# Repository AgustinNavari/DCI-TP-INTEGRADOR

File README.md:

# Shield de motor paso a paso para Arduino Nano ESP32

Trabajo práctico integrador de la asignatura Diseño de Circuitos Impresos del posgrado de FIUBA.

- **Autor:** Agustín Navari
- **Cursada:** octubre–diciembre de 2026
- **Driver:** Toshiba TB67S249FTG
- **Plataforma:** Arduino Nano ESP32
- **Estado:** diseño del PCB y ruteo en desarrollo.

## Descripción y objetivo

El proyecto consiste en el diseño de una placa para controlar un motor paso a paso bipolar mediante un Arduino Nano ESP32, utilizando el driver TB67S249FTG.

El diseño toma como referencia el módulo Pololu 2973 y adapta sus interfaces al formato de una placa portadora para el Nano ESP32. Incluye dos conectores hembra de 15 posiciones para alojar el módulo y un conector adicional de 2 × 15 posiciones que permite acceder a sus pines.

El objetivo es desarrollar el esquemático, seleccionar los componentes y diseñar el PCB, contemplando los requisitos eléctricos, térmicos, mecánicos y de fabricación.

## Características del diseño

- Alimentación del motor de 24 V nominales.
- Alimentación del Nano mediante USB o una entrada externa independiente.
- Protección contra inversión de polaridad en la alimentación del motor mediante un MOSFET.
- Control de movimiento mediante las señales STEP, DIR y ENABLE.
- Configuración de funciones del driver mediante jumpers.
- Conexión opcional de señales de configuración al Nano.
- Ajuste del límite de corriente mediante potenciómetro.
- Conector independiente para las salidas de diagnóstico.
- PCB de dos capas, previsto para cobre de 1 oz y espesor de placa de 1,6 mm.

## Interfaz con el Arduino Nano ESP32

Las entradas de control del driver admiten las señales de lógica de 3,3 V del Nano ESP32.

Las señales STEP, DIR y ENABLE se conectan directamente al microcontrolador. Otras funciones pueden conectarse mediante jumpers, permitiendo liberar esos pines cuando no se utilizan para controlar el driver.

Los pines del Nano también se encuentran disponibles en un conector de expansión. Los pines conectados permanentemente al driver comparten su función con este conector y no quedan disponibles como señales independientes.

Las salidas de diagnóstico MO, LO1 y LO2 utilizan resistencias de pull-up a la alimentación interna de 5 V del driver. Se exponen en un conector independiente y no se conectan directamente al Nano.

La alimentación VCC generada por el Toshiba se utiliza únicamente para el circuito del driver y su configuración. No se conecta a la salida de 3,3 V ni a VUSB del Nano.

## Alimentación

La placa dispone de entradas separadas para la alimentación del motor y del Nano ESP32. Ambas comparten GND.

- **Motor:** entrada de 24 V nominales, con protección contra inversión de polaridad.
- **Nano:** alimentación mediante USB o una fuente externa regulada de 9–12 V conectada a su entrada VIN a través de un diodo de protección.

La entrada de alimentación del Nano no debe conectarse directamente a la fuente de 24 V del motor.

## Criterios de diseño del PCB

Se adopta una corriente objetivo de 1,7 A por fase para dimensionar las conexiones de salida del motor.

El cálculo inicial de ancho de pistas considera cobre de 35 µm, capas externas y un incremento de temperatura de 10 °C. Las conexiones próximas al encapsulado utilizan estrechamientos cortos que se ensanchan al disponer de espacio.

La corriente continua admisible de la placa queda pendiente de validación térmica. El valor de referencia del módulo comercial no garantiza el mismo desempeño en este diseño.

La distribución de componentes y el ruteo contemplan:

- Capacitores de desacople próximos a los pines correspondientes.
- Conexiones cortas y amplias en los recorridos de potencia.
- Planos de GND y vías para conectar ambas caras.
- Disipación del driver mediante su pad expuesto y cobre asociado.
- Separación entre señales de configuración y recorridos de potencia.
- Reserva del área necesaria para la antena del Nano ESP32.
- Acceso a conectores, jumpers y potenciómetro.

## Estado del proyecto

El esquemático fue elaborado y revisado mediante ERC y una revisión funcional de las conexiones.

Actualmente se trabaja en la distribución de componentes y el ruteo del PCB. Quedan pendientes la revisión final del layout, la verificación DRC y la generación de los archivos de fabricación.

El diseño todavía no cuenta con validación experimental de funcionamiento ni de desempeño térmico.

## Estructura del repositorio

- **doc/**: propuesta, cálculos, decisiones de ingeniería y documentación propia del diseño.
- **info/**: hojas de datos y documentación de referencia de terceros.
- **pcb/**: proyecto KiCad, bibliotecas propias, modelos 3D y archivos de fabricación generados.

La propuesta del trabajo se encuentra en [doc/propuesta/README.md](doc/propuesta/README.md).

## Apertura del proyecto

Abrir el archivo `.kicad_pro` ubicado en el directorio `pcb/` desde el administrador de proyectos de KiCad.

Las bibliotecas y los modelos 3D propios deben mantenerse dentro del repositorio y utilizar rutas relativas al proyecto mediante `${KIPRJMOD}`.

Los archivos del proyecto se desarrollan con KiCad 10. Se recomienda utilizar la misma versión principal al trabajar desde distintas computadoras.

## Licencia

La licencia de hardware abierto del proyecto se encuentra pendiente de selección.

Antes de la entrega final se incorporará su identificación en esta sección y el texto completo de la licencia en un archivo ubicado en la raíz del repositorio.

La documentación de terceros conserva sus respectivas licencias y avisos de autoría.

## Referencias

- [Pololu 2973 — TB67S249FTG Stepper Motor Driver Carrier, Full Breakout](https://www.pololu.com/product/2973)
- [Arduino Nano ESP32 — documentación oficial](https://docs.arduino.cc/hardware/nano-esp32/)
- [Consigna del trabajo práctico integrador](https://github.com/cese-dci/DCI-TP-INTEGRADOR)

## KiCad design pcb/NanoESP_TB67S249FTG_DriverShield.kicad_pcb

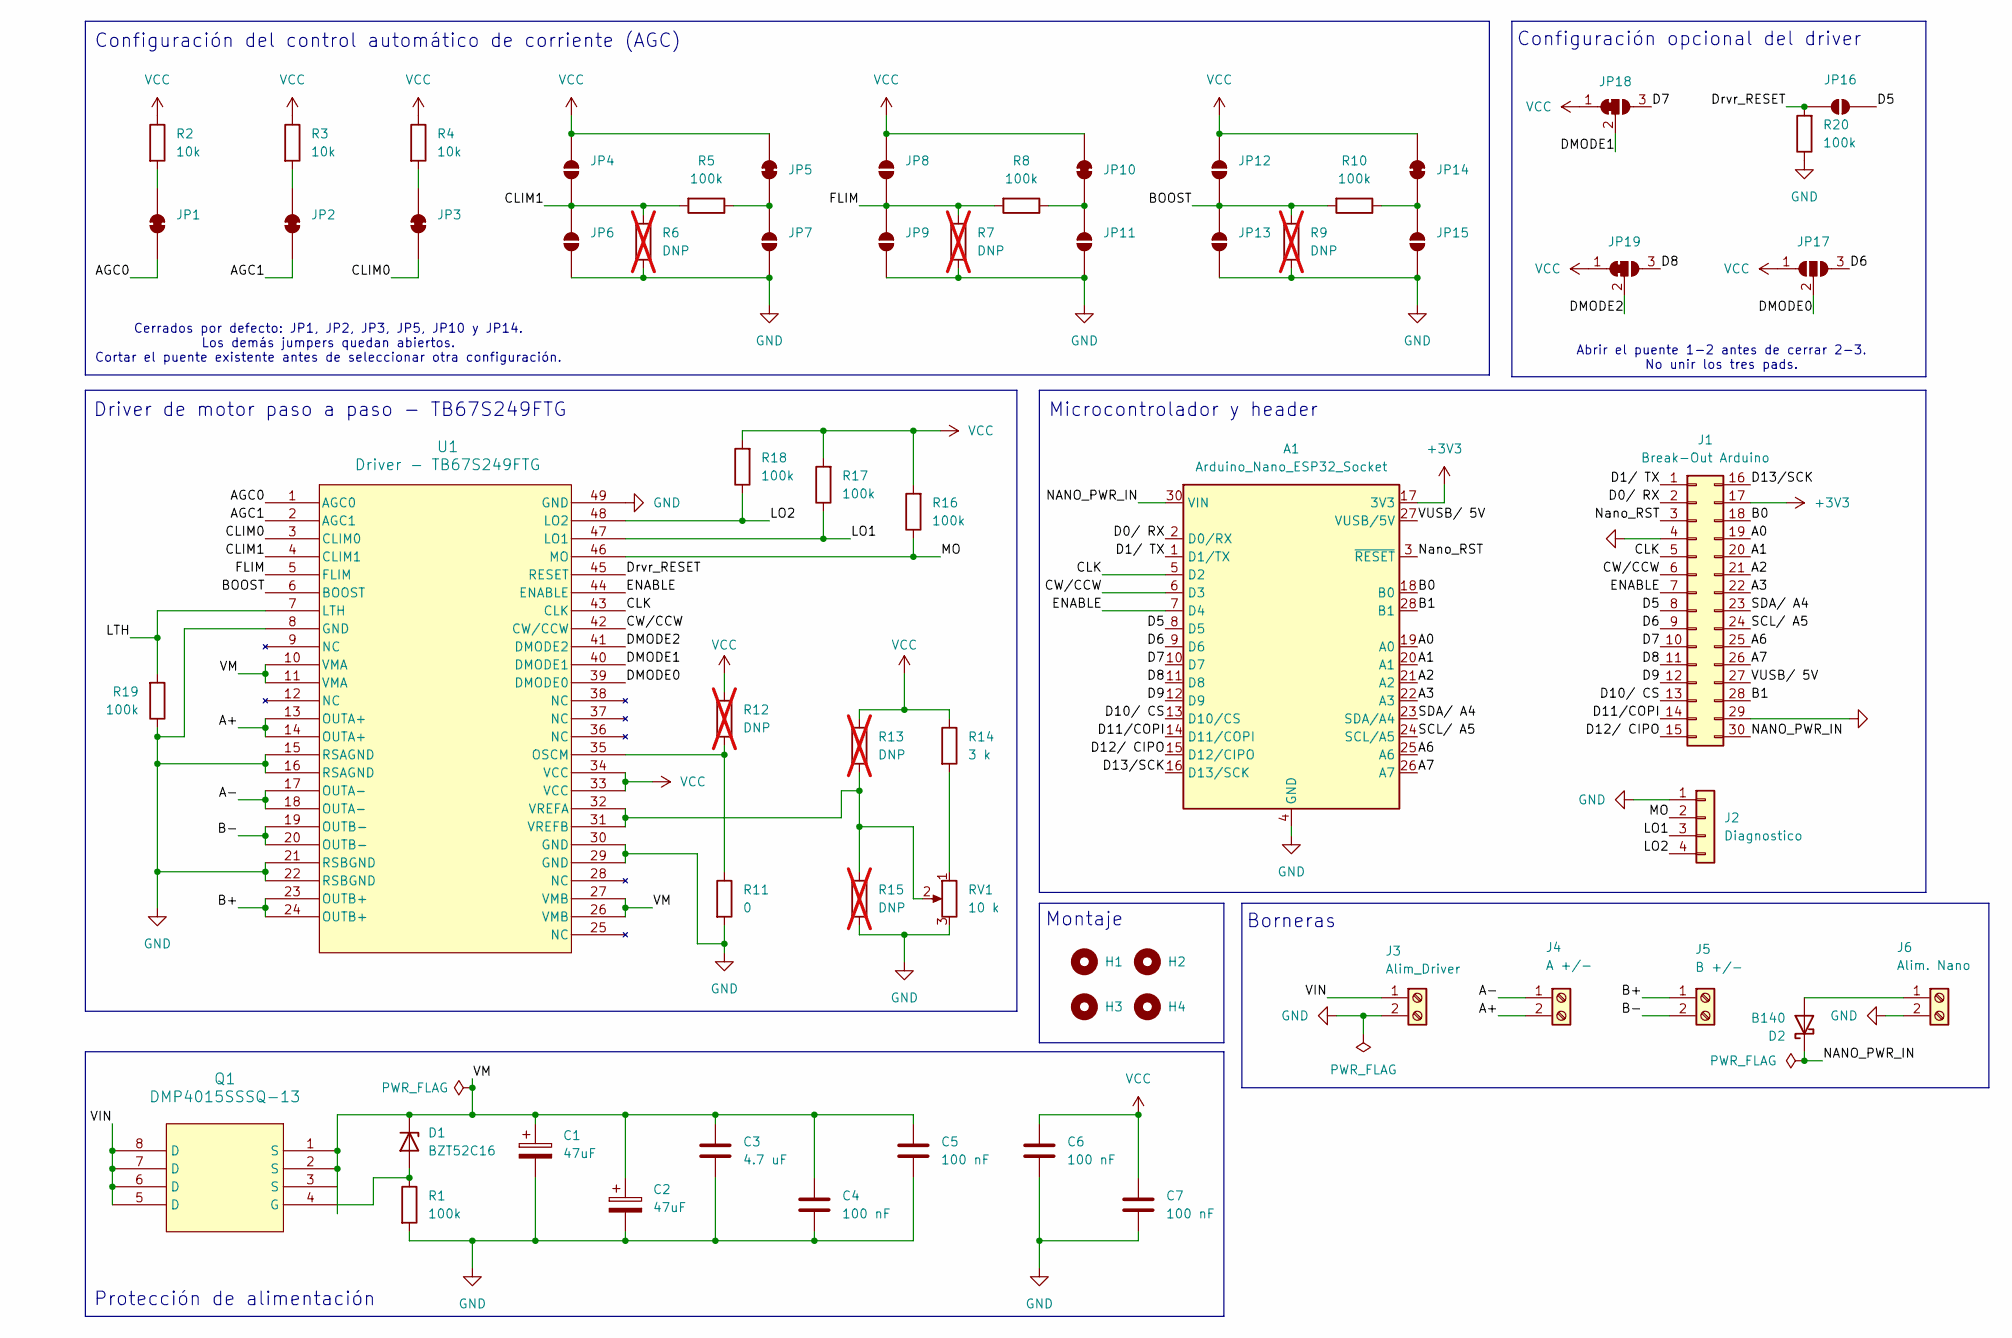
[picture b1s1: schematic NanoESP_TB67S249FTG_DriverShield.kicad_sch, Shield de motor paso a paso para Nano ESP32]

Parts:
A1: Arduino_Nano_ESP32_Socket; Arduino_Nano_headers_hembra
C1, C2: 47uF; CP_Elec_8x6.5; MPN EEE-FK1H470P
C3: 4.7 uF; C_1210_3225Metric_Pad1.33x2.70mm_HandSolder; MPN GRM32ER71H475KA88K
C4, C5, C6, C7: 100 nF; C_0805_2012Metric_Pad1.18x1.45mm_HandSolder; MPN C0805C104K5RACTU
D1: BZT52C16; Nexperia_CFP3_SOD-123W
D2: B140; D_SMA_Handsoldering; MPN B140-13-F
H1, H2, H3, H4: MountingHole; MountingHole_3.2mm_M3
J1: Break-Out Arduino; Breakout_Nano_2x15
J2: Diagnostico; PinHeader_1x04_P2.54mm_Vertical
J3: Alim_Driver; OST_OSTTE020104_espejo
J4: A +/-; OST_OSTTE020104_espejo
J5: B +/-; OST_OSTTE020104_espejo
J6: Alim. Nano; OST_OSTTE020104_espejo
JP1: JP_AGC0; SolderJumper-2_P1.3mm_Bridged_RoundedPad1.0x1.5mm
JP2: JP_AGC1; SolderJumper-2_P1.3mm_Bridged_RoundedPad1.0x1.5mm
JP3: JP_CLIM0; SolderJumper-2_P1.3mm_Bridged_RoundedPad1.0x1.5mm
JP4, JP6, JP7: JP_CLIM1; SolderJumper-2_P1.3mm_Open_RoundedPad1.0x1.5mm
JP5: JP_CLIM1; SolderJumper-2_P1.3mm_Bridged_RoundedPad1.0x1.5mm
JP8, JP9, JP11: JP_FLIM; SolderJumper-2_P1.3mm_Open_RoundedPad1.0x1.5mm
JP10: JP_FLIM; SolderJumper-2_P1.3mm_Bridged_RoundedPad1.0x1.5mm
JP12, JP13, JP15: JP_BOOST; SolderJumper-2_P1.3mm_Open_RoundedPad1.0x1.5mm
JP14: JP_BOOST; SolderJumper-2_P1.3mm_Bridged_RoundedPad1.0x1.5mm
JP16: JP_D5; SolderJumper-2_P1.3mm_Open_RoundedPad1.0x1.5mm
JP17: JP_D6; SolderJumper-3_P1.3mm_Open_RoundedPad1.0x1.5mm_NumberLabels
JP18: JP_D7; SolderJumper-3_P1.3mm_Bridged12_RoundedPad1.0x1.5mm
JP19: JP_D8; SolderJumper-3_P1.3mm_Bridged12_RoundedPad1.0x1.5mm
Q1: DMP4015SSSQ-13; SO8_DIO-M
R1, R5, R8, R10, R16, R17, R18, R19, R20: 100k; R_0805_2012Metric_Pad1.20x1.40mm_HandSolder
R2, R3, R4: 10k; R_0805_2012Metric_Pad1.20x1.40mm_HandSolder
R6, R7, R9, R12, R13, R15: DNP; R_0805_2012Metric_Pad1.20x1.40mm_HandSolder; not fitted
R11: 0; R_0805_2012Metric_Pad1.20x1.40mm_HandSolder
R14: 3 k; R_0805_2012Metric_Pad1.20x1.40mm_HandSolder
RV1: 10 k; Potentiometer_Bourns_3314G_Vertical; MPN 3314G-1-103E
U1: Driver - TB67S249FTG; P-VQFN48-0707-0p50-004_TOS-M

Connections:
+3V3: A1.17 (3V3), J1.17
/A0: A1.19 (A0), J1.19
/A1: A1.20 (A1), J1.20
/A2: A1.21 (A2), J1.21
/A3: A1.22 (A3), J1.22
/A6: A1.25 (A6), J1.25
/A7: A1.26 (A7), J1.26
/A+: J4.2, U1.13 (OUTA+), U1.14 (OUTA+)
/A-: J4.1, U1.17 (OUTA-), U1.18 (OUTA-)
/AGC0: JP1.2 (B), U1.1 (AGC0)
/AGC1: JP2.2 (B), U1.2 (AGC1)
/B0: A1.18 (B0), J1.18
/B1: A1.28 (B1), J1.28
/B+: J5.1, U1.23 (OUTB+), U1.24 (OUTB+)
/B-: J5.2, U1.19 (OUTB-), U1.20 (OUTB-)
/BOOST: JP12.2 (B), JP13.1 (A), R9.1, R10.2, U1.6 (BOOST)
/CLIM0: JP3.2 (B), U1.3 (CLIM0)
/CLIM1: JP4.2 (B), JP6.1 (A), R5.2, R6.1, U1.4 (CLIM1)
/CLK: A1.5 (D2), J1.5, U1.43 (CLK)
/CW/CCW: A1.6 (D3), J1.6, U1.42 (CW/CCW)
/D0/ RX: A1.2 (D0/RX), J1.2
/D1/ TX: A1.1 (D1/TX), J1.1
/D5: A1.8 (D5), J1.8, JP16.1 (A)
/D6: A1.9 (D6), J1.9, JP17.3 (B)
/D7: A1.10 (D7), J1.10, JP18.3 (B)
/D8: A1.11 (D8), J1.11, JP19.3 (B)
/D9: A1.12 (D9), J1.12
/D10/ CS: A1.13 (D10/CS), J1.13
/D11/COPI: A1.14 (D11/COPI), J1.14
/D12/ CIPO: A1.15 (D12/CIPO), J1.15
/D13/SCK: A1.16 (D13/SCK), J1.16
/DMODE0: JP17.2 (C), U1.39 (DMODE0)
/DMODE1: JP18.2 (C), U1.40 (DMODE1)
/DMODE2: JP19.2 (C), U1.41 (DMODE2)
/Drvr_RESET: JP16.2 (B), R20.2, U1.45 (RESET)
/ENABLE: A1.7 (D4), J1.7, U1.44 (ENABLE)
/FLIM: JP8.2 (B), JP9.1 (A), R7.1, R8.2, U1.5 (FLIM)
/LO1: J2.3, R17.1, U1.47 (LO1)
/LO2: J2.4, R18.1, U1.48 (LO2)
/LTH: R19.2, U1.7 (LTH)
/MO: J2.2, R16.1, U1.46 (MO)
/NANO_PWR_IN: A1.30 (VIN), D2.1 (K), J1.30
/Nano_RST: A1.3 (~RESET), J1.3
/SCL/ A5: A1.24 (SCL/A5), J1.24
/SDA/ A4: A1.23 (SDA/A4), J1.23
/VIN: J3.1, Q1.5 (D), Q1.6 (D), Q1.7 (D), Q1.8 (D)
/VM: C1.1, C2.1, C3.1, C4.1, C5.1, D1.1 (K), Q1.1 (S), Q1.2 (S), Q1.3 (S), U1.10 (VMA), U1.11 (VMA), U1.26 (VMB), U1.27 (VMB)
/VUSB/ 5V: A1.27 (VUSB/5V), J1.27
GND: A1.4 (GND), A1.29 (GND), C1.2, C2.2, C3.2, C4.2, C5.2, C6.2, C7.2, J1.4, J1.29, J2.1, J3.2, J6.2, JP6.2 (B), JP7.2 (B), JP9.2 (B), JP11.2 (B), JP13.2 (B), JP15.2 (B), R1.2, R6.2, R7.2, R9.2, R11.2, R15.2, R19.1, R20.1, RV1.3, U1.8 (GND), U1.15 (RSAGND), U1.16 (RSAGND), U1.21 (RSBGND), U1.22 (RSBGND), U1.29 (GND), U1.30 (GND), U1.49 (GND)
unnamed: D1.2 (A), Q1.4 (G), R1.1
unnamed: D2.2 (A), J6.1
unnamed: JP1.1 (A), R2.2
unnamed: JP2.1 (A), R3.2
unnamed: JP3.1 (A), R4.2
unnamed: JP5.2 (B), JP7.1 (A), R5.1
unnamed: JP10.2 (B), JP11.1 (A), R8.1
unnamed: JP14.2 (B), JP15.1 (A), R10.1
unnamed: R14.2, RV1.1
unnamed: R11.1, R12.2, U1.35 (OSCM)
unnamed: R13.2, R15.1, RV1.2, U1.31 (VREFB), U1.32 (VREFA)
VCC: C6.1, C7.1, JP4.1 (A), JP5.1 (A), JP8.1 (A), JP10.1 (A), JP12.1 (A), JP14.1 (A), JP17.1 (A), JP18.1 (A), JP19.1 (A), R2.1, R3.1, R4.1, R12.1, R13.1, R14.1, R16.2, R17.2, R18.2, U1.33 (VCC), U1.34 (VCC)

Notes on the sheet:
Configuración opcional del driver
Borneras
Configuración del control automático de corriente (AGC)
Montaje
Cerrados por defecto: JP1, JP2, JP3, JP5, JP10 y JP14. Los demás jumpers quedan abiertos. Cortar el puente existente antes de seleccionar otra configuración.
Driver de motor paso a paso - TB67S249FTG
Abrir el puente 1-2 antes de cerrar 2-3. No unir los tres pads.
Protección de alimentación
Microcontrolador y header

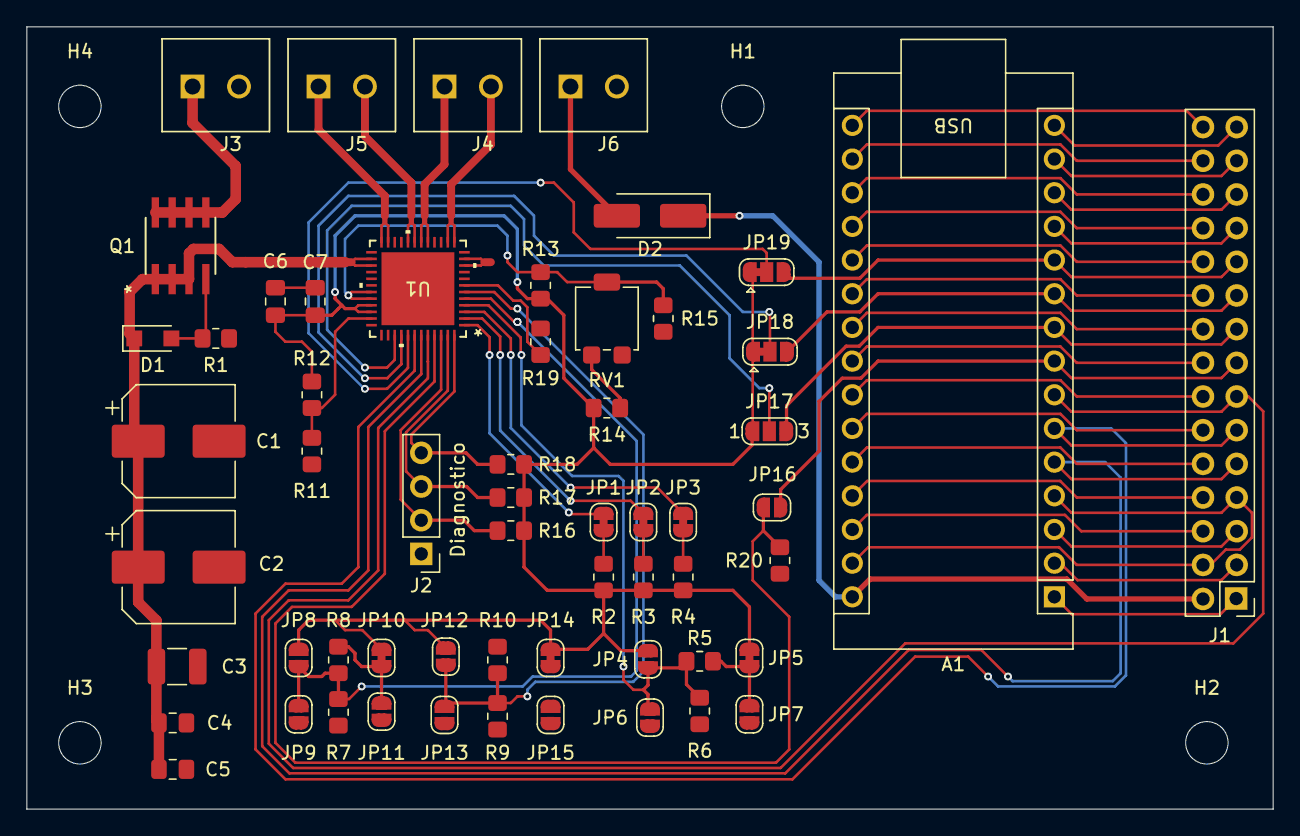
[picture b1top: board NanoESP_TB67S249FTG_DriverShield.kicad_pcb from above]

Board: 2 copper layers, 94.0 x 59.0 mm, 62 parts (0 on the bottom side), 61 nets.
